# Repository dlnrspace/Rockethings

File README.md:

# Rockethings
 
👋 Oh hello there !

This is my repository about things I made for student rockets.

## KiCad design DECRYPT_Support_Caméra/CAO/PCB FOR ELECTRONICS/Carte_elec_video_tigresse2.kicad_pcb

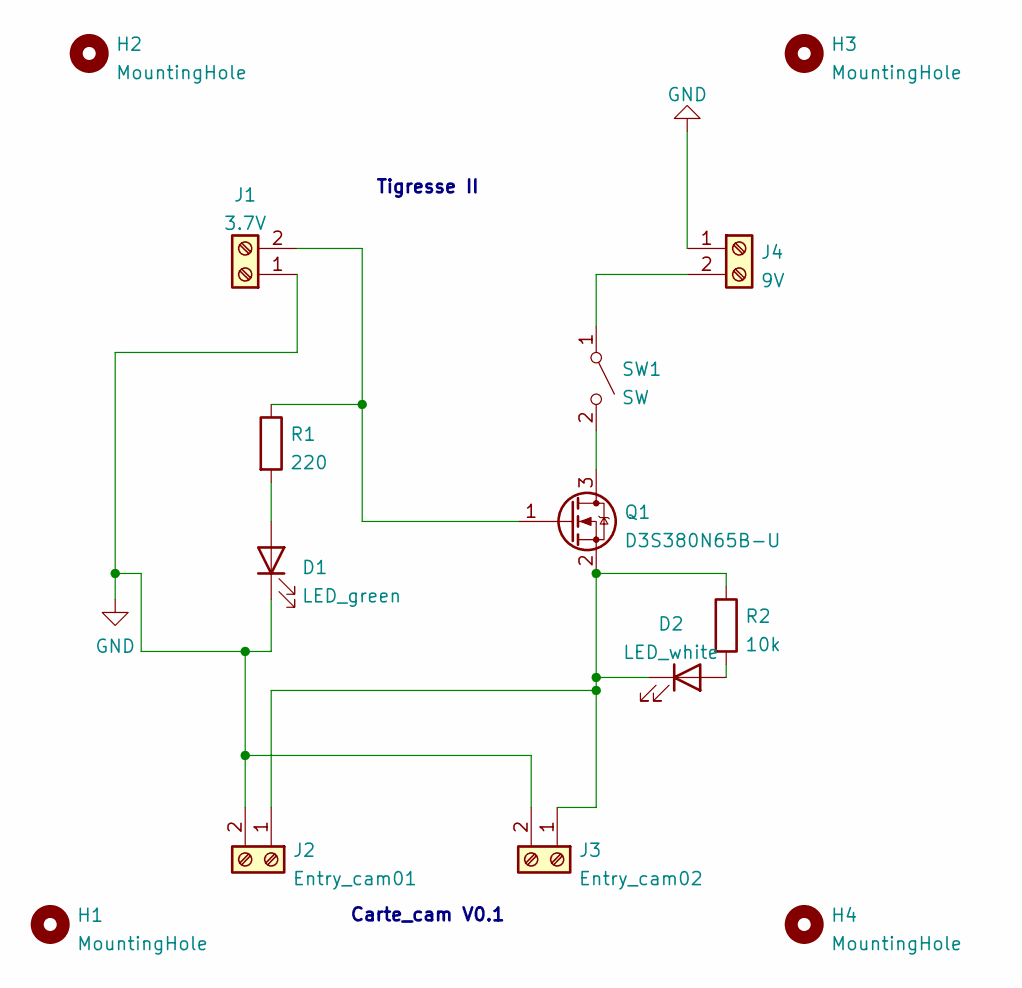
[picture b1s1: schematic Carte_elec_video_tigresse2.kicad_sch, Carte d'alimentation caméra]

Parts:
D1: LED_green; LED_D3.0mm
D2: LED_white; LED_D3.0mm
H1, H2, H3, H4: MountingHole; MountingHole_2.2mm_M2_Pad
J1: 3.7V; JST_PH_S2B-PH-K_1x02_P2.00mm_Horizontal
J2: Entry_cam01; JST_PH_S2B-PH-K_1x02_P2.00mm_Horizontal
J3: Entry_cam02; JST_PH_S2B-PH-K_1x02_P2.00mm_Horizontal
J4: 9V; JST_PH_S2B-PH-K_1x02_P2.00mm_Horizontal
Q1: D3S380N65B-U; TO-220-3_Vertical
R1: 220; R_Axial_DIN0204_L3.6mm_D1.6mm_P5.08mm_Horizontal
R2: 10k; R_Axial_DIN0204_L3.6mm_D1.6mm_P5.08mm_Horizontal
SW1: SW; SW_CuK_OS102011MA1QN1_SPDT_Angled

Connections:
GND: D1.1 (K), J1.1, J2.2, J3.2, J4.1
unnamed: D1.2 (A), R1.2
unnamed: D2.1 (K), J2.1, J3.1, Q1.2 (S), R2.1
unnamed: D2.2 (A), R2.2
unnamed: J1.2, Q1.1 (G), R1.1
unnamed: J4.2, SW1.1 (A)
unnamed: Q1.3 (D), SW1.2 (B)

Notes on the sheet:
Tigresse II
Carte_cam V0.1

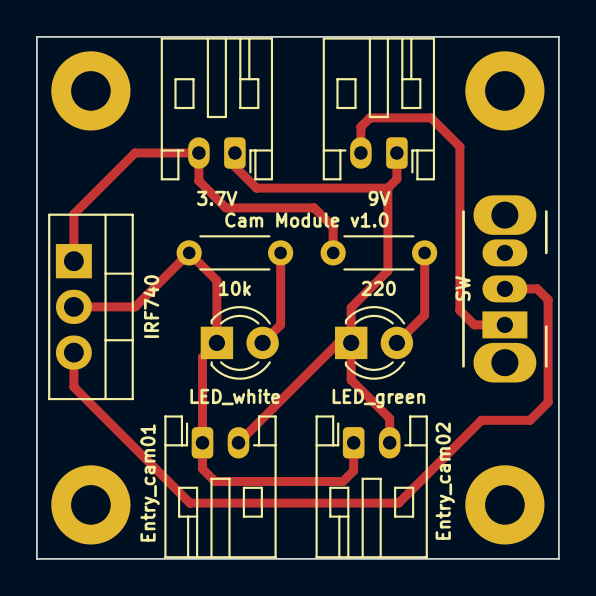
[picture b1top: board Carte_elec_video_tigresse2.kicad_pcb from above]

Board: 2 copper layers, 29.0 x 29.0 mm, 14 parts (0 on the bottom side), 7 nets.
